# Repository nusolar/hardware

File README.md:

# hardware
schematics, board files, BOMs

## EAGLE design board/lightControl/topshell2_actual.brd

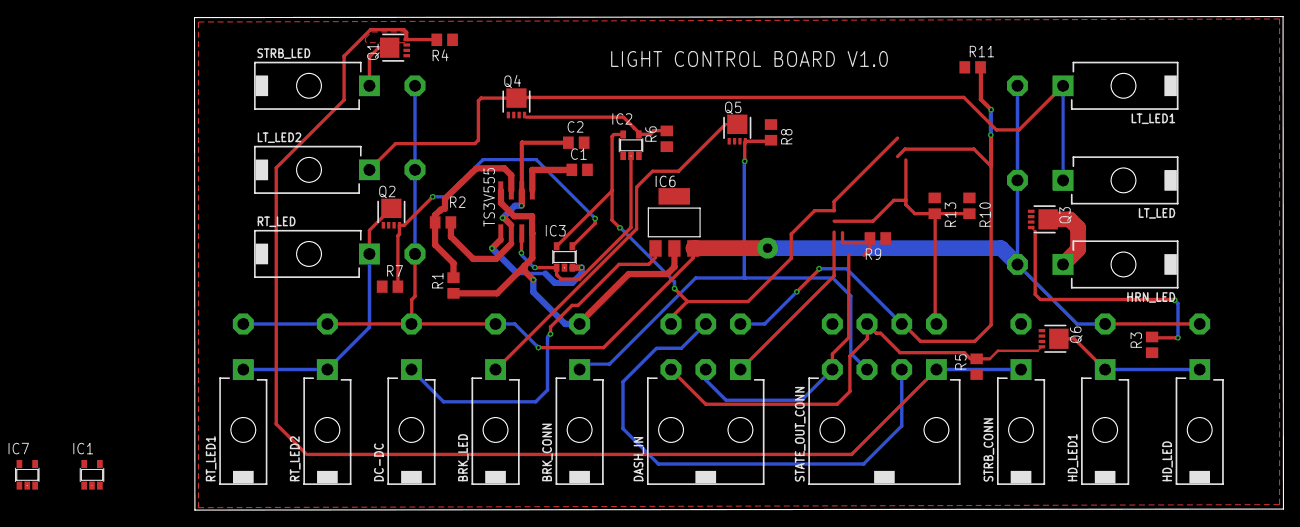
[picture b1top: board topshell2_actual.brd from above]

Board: 2 copper layers, 131.6 x 59.6 mm, 42 parts (0 on the bottom side), 26 nets.

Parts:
BRK_CONN: 39-30-02?; 39-30-?02?
BRK_LED: 39-30-02?; 39-30-?02?
C1: 10nF; C0805
C2: 2.2uF; C0805
DASH_IN: 39-30-06?; 39-30-?06?
DC-DC: 39-30-02?; 39-30-?02?
HD_LED, HD_LED1: 39-30-02?; 39-30-?02?
HRN_LED: 39-30-02?; 39-30-?02?
IC1, IC7: 74AHC1G32DBV; SOT23-5
IC2, IC3: 74AHC1G08DBV; SOT23-5
IC6: REG1117; SOT223
LT_LED, LT_LED1, LT_LED2: 39-30-02?; 39-30-?02?
Q1, Q2, Q3, Q4, Q5, Q6: PSMN013-30MLC; LFPAK33
R1: 100K; R0805
R2: 220K; R0805
R3, R4, R5, R6, R7, R8, R9, R10, R11, R13: 1K; R0805
RT_LED, RT_LED1, RT_LED2: 39-30-02?; 39-30-?02?
STATE_OUT_CONN: 39-30-08?; 39-30-?08?
STRB_CONN: 39-30-02?; 39-30-?02?
STRB_LED: 39-30-02?; 39-30-?02?
TS3V555: LM555D; SO08

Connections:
GND: C1.2, C2.2, IC1.3, IC2.3, IC3.3, IC7.3, Q1.1, Q1.2, Q1.3, Q2.1, Q2.2, Q2.3, Q3.1, Q3.2, Q3.3, Q4.1, Q4.2, Q4.3, Q5.1, Q5.2, Q5.3, Q6.1, Q6.2, Q6.3, R3.1, R4.1, R5.1, R6.1, R7.1, R8.1, R9.1, R10.1, R11.1, R13.1, STATE_OUT_CONN.8, STRB_CONN.2, TS3V555.1
unnamed: R1.2, R2.1, TS3V555.7
unnamed: Q1.MB, STRB_LED.1
unnamed: C2.1, R2.2, TS3V555.2, TS3V555.6
unnamed: IC2.2, IC3.1, TS3V555.3
unnamed: HRN_LED.1, Q3.MB
unnamed: Q1.4, R4.2, STATE_OUT_CONN.1, STRB_CONN.1
unnamed: DASH_IN.2, IC1.2, R9.2, STATE_OUT_CONN.4
unnamed: DASH_IN.1, IC1.1, IC7.2, R10.2, R13.2, STATE_OUT_CONN.5
unnamed: IC1.4, IC2.1
unnamed: IC3.2, IC7.4
unnamed: DASH_IN.4, IC7.1, R11.2, STATE_OUT_CONN.6
unnamed: IC2.4, Q4.4, R6.2
unnamed: IC3.4, Q2.4, R7.2
unnamed: LT_LED.1, LT_LED1.1, LT_LED2.1, Q4.MB
unnamed: Q2.MB, RT_LED.1, RT_LED1.1, RT_LED2.1
unnamed: BRK_LED.1, Q5.MB
unnamed: HD_LED.1, HD_LED1.1, Q6.MB
unnamed: DC-DC.1, IC6.1
unnamed: DASH_IN.3, Q6.4, R5.2, STATE_OUT_CONN.7
unnamed: Q3.4, R3.2
unnamed: DASH_IN.5, STATE_OUT_CONN.2
unnamed: BRK_CONN.1, Q5.4, R8.2, STATE_OUT_CONN.3
unnamed: BRK_LED.2, DC-DC.2, HD_LED.2, HD_LED1.2, HRN_LED.2, IC6.3, LT_LED.2, LT_LED1.2, LT_LED2.2, RT_LED.2, RT_LED1.2, RT_LED2.2, STRB_LED.2
TS3V555: C1.1, TS3V555.5
VDD: BRK_CONN.2, DASH_IN.6, IC1.5, IC2.5, IC3.5, IC6.2, IC7.5, R1.1, TS3V555.4, TS3V555.8

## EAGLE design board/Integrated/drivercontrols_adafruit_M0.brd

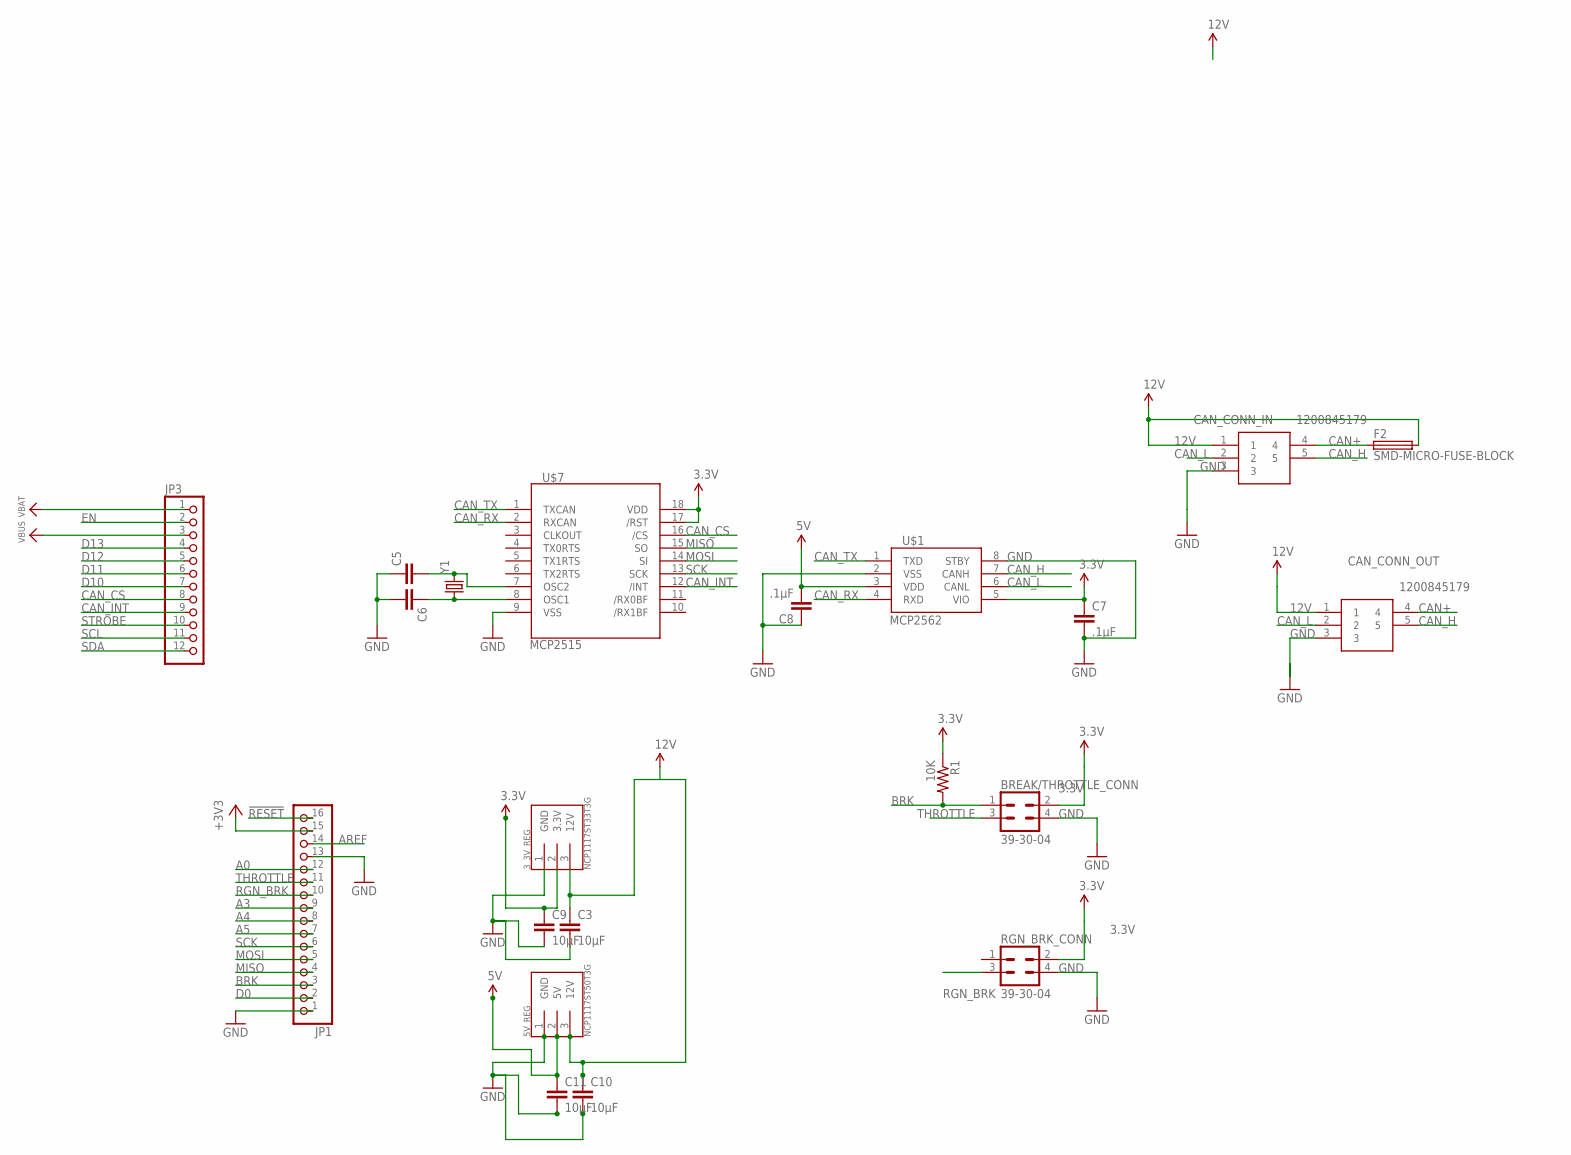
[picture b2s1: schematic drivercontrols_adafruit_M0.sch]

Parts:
3_3V_REG: NCP1117ST33T3G; SOT223
5V_REG: NCP1117ST50T3G; SOT223
BREAK/THROTTLE_CONN: 39-30-04; 39-30-?04?
C3, C9, C10, C11: 10µF; 0805
C5, C6: CAP0805; 0805
C7, C8: .1µF; 0805
CAN_CONN_IN: 1200845179
CAN_CONN_OUT: 1200845179
F2: SMD-MICRO-FUSE-BLOCK; OMNIBLOK
JP1: HEADER-1X16ROUND; 1X16_ROUND
JP3: HEADER-1X12; 1X12_ROUND
R1: 10K; M0805
RGN_BRK_CONN: 39-30-04; 39-30-?04?
U$1: MCP2562; SOIC8
U$7: MCP2515; SO-18W
Y1: CRYSTALHC49US; HC49US

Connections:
3.3V: 3_3V_REG.2 (3.3V), BREAK/THROTTLE_CONN.2, C7.1, C9.1, R1.1, RGN_BRK_CONN.2, U$1.5 (VIO), U$7.17 (/RST), U$7.18 (VDD)
5V: 5V_REG.2 (5V), C8.2, C11.1, U$1.3 (VDD)
12V: 3_3V_REG.3 (12V), 5V_REG.3 (12V), C3.1, C10.1, CAN_CONN_IN.1, CAN_CONN_OUT.1, F2.P$2 (2)
!RESET: JP1.16
+3V3: JP1.15
A0: JP1.12
A3: JP1.9
A4: JP1.8
A5: JP1.7
AREF: JP1.14
BRK: BREAK/THROTTLE_CONN.1, JP1.3, R1.2
CAN+: CAN_CONN_IN.4, CAN_CONN_OUT.4, F2.P$1 (1)
CAN_CS: JP3.8, U$7.16 (/CS)
CAN_H: CAN_CONN_IN.5, CAN_CONN_OUT.5, U$1.7 (CANH)
CAN_INT: JP3.9, U$7.12 (/INT)
CAN_L: CAN_CONN_IN.2, CAN_CONN_OUT.2, U$1.6 (CANL)
CAN_RX: U$1.4 (RXD), U$7.2 (RXCAN)
CAN_TX: U$1.1 (TXD), U$7.1 (TXCAN)
D0: JP1.2
D10: JP3.7
D11: JP3.6
D12: JP3.5
D13: JP3.4
EN: JP3.2
GND: 3_3V_REG.1 (GND), 5V_REG.1 (GND), BREAK/THROTTLE_CONN.4, C3.2, C5.1, C6.2, C7.2, C8.1, C9.2, C10.2, C11.2, CAN_CONN_IN.3, CAN_CONN_OUT.3, JP1.1, JP1.13, RGN_BRK_CONN.4, U$1.2 (VSS), U$1.8 (STBY), U$7.9 (VSS)
MISO: JP1.4, U$7.15 (SO)
MOSI: JP1.5, U$7.14 (SI)
unnamed: C5.2, U$7.7 (OSC2), Y1.2
unnamed: C6.1, U$7.8 (OSC1), Y1.1
RGN_BRK: JP1.10, RGN_BRK_CONN.3
SCK: JP1.6, U$7.13 (SCK)
SCL: JP3.11
SDA: JP3.12
STROBE: JP3.10
THROTTLE: BREAK/THROTTLE_CONN.3, JP1.11
VBAT: JP3.1
VBUS: JP3.3

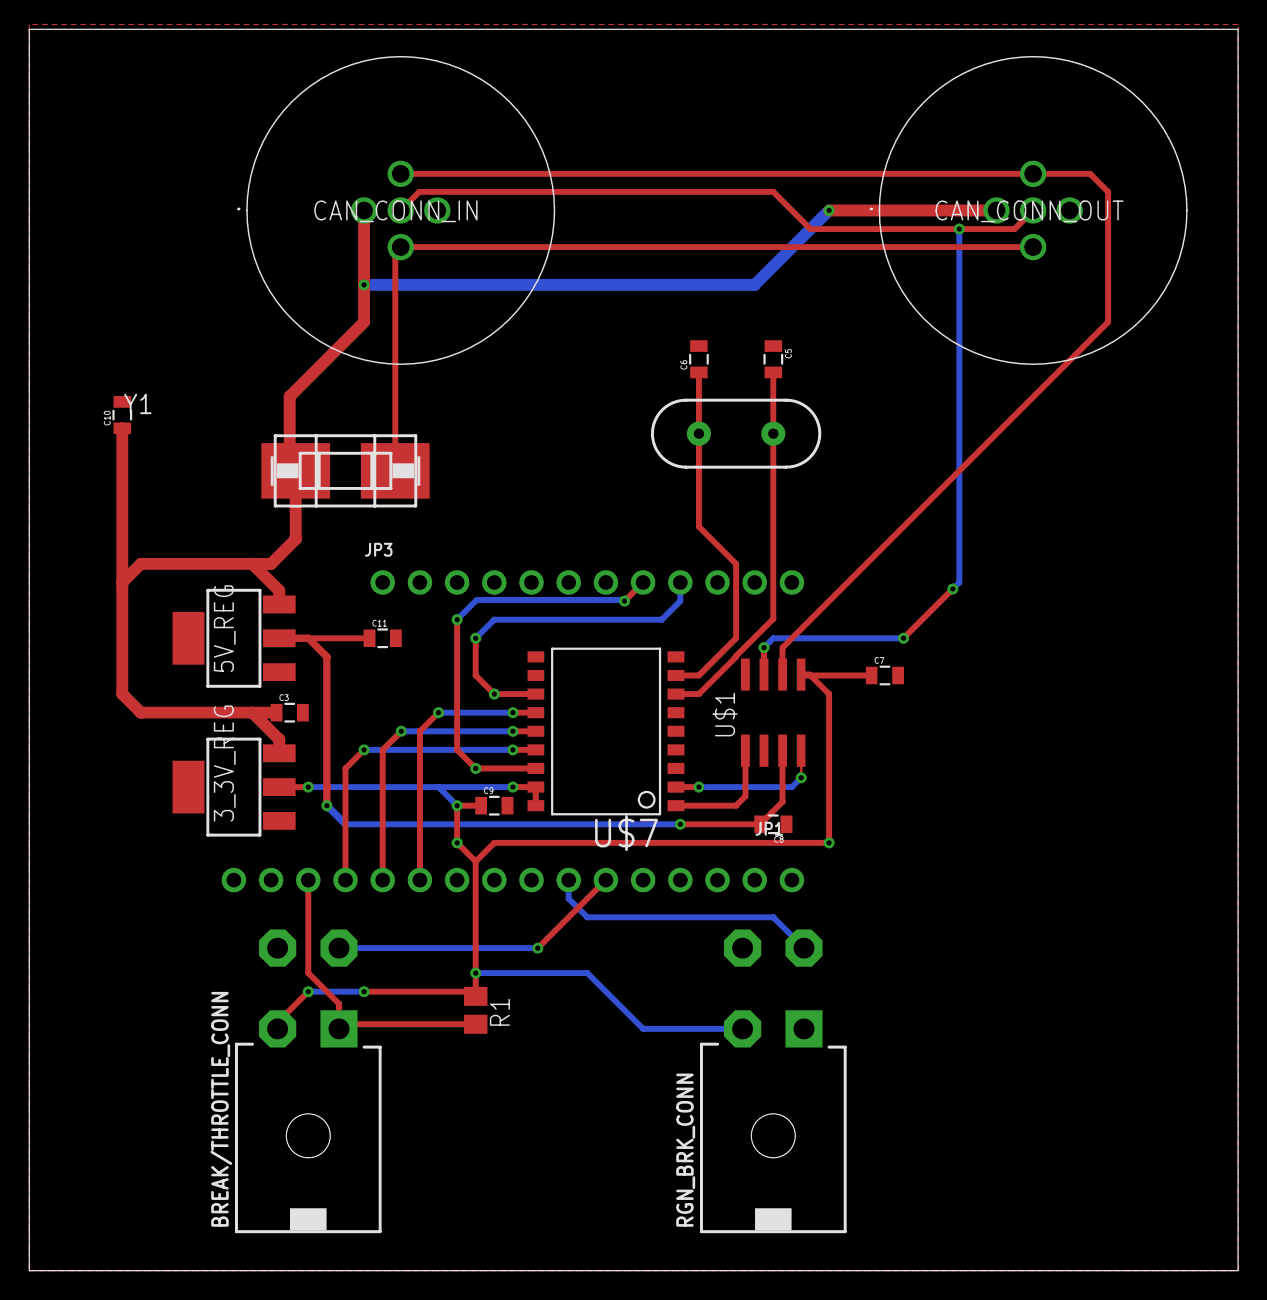
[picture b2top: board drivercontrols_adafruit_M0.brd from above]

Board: 2 copper layers, 82.5 x 84.8 mm, 21 parts (0 on the bottom side), 19 nets.

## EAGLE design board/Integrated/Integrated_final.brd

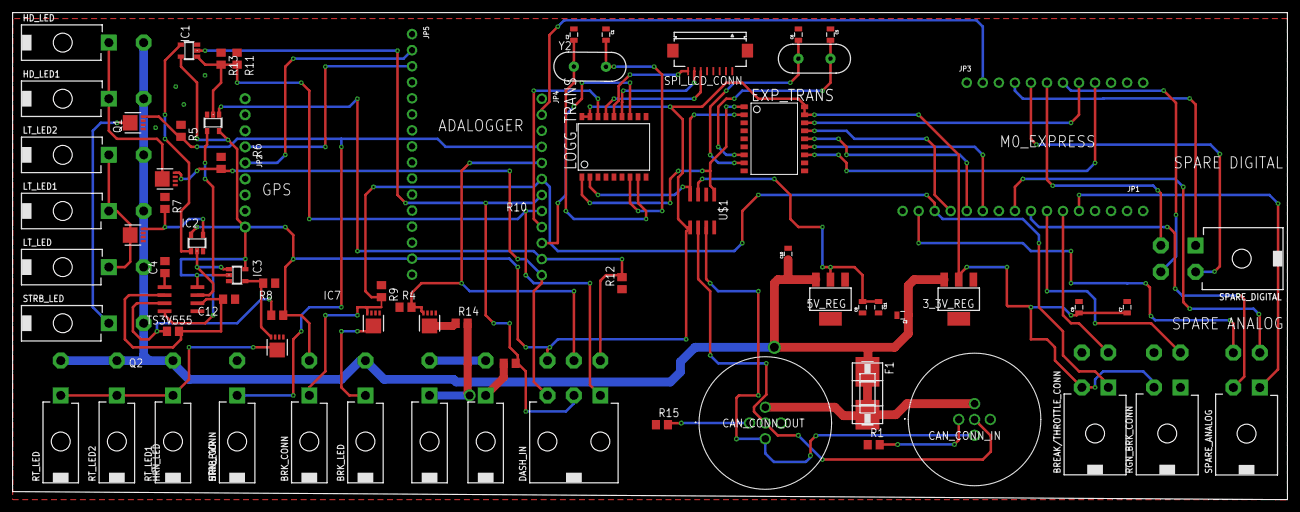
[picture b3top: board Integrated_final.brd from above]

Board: 2 copper layers, 201.9 x 77.1 mm, 73 parts (0 on the bottom side), 60 nets.

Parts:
3_3V_REG: NCP1117ST33T3G; SOT223
5V_REG: NCP1117ST50T3G; SOT223
BREAK/THROTTLE_CONN: 39-30-04?; 39-30-?04?
BRK_CONN: 39-30-02?; 39-30-?02?
BRK_LED: 39-30-02?; 39-30-?02?
C1, C2, C5, C6: 18 pF; 0805
C3, C9, C10, C11: 10µF; 0805
C4: 10nF; C0805
C7, C8: .1µF; 0805
C12: 2.2uF; C0805
CAN_CONN_IN: 1200845179
CAN_CONN_OUT: 1200845179
DASH_IN: 39-30-06?; 39-30-?06?
EXP_TRANS: MCP2515; SO-18W
F1: SMD-MICRO-FUSE-BLOCK; OMNIBLOK
HD_LED, HD_LED1: 39-30-02?; 39-30-?02?
HRN_LED: 39-30-02?; 39-30-?02?
HRN_PWR: 39-30-02?; 39-30-?02?
IC1, IC7: 74AHC1G32DBV; SOT23-5
IC2, IC3: 74AHC1G08DBV; SOT23-5
JP1, JP5: 1X16_ROUND
JP2: 1X09_ROUND_70
JP3, JP4: 1X12_ROUND
LOGG_TRANS: MCP2515; SO-18W
LT_LED, LT_LED1, LT_LED2: 39-30-02?; 39-30-?02?
Q1, Q2, Q3, Q4, Q5, Q6: PSMN013-30MLC; LFPAK33
R1, R15: 0; R0805
R2: 220K; R0805
R3: 100K; R0805
R4, R5, R6, R7, R8, R9, R10, R11, R12, R13, R14: 1K; R0805
RGN_BRK_CONN: 39-30-04?; 39-30-?04?
RT_LED, RT_LED1, RT_LED2: 39-30-02?; 39-30-?02?
SPARE_ANALOG: 39-30-04?; 39-30-?04?
SPARE_DIGITAL: 39-30-04?; 39-30-?04?
SPI_LCD_CONN: FH12-08S-1SH
STRB_CONN: 39-30-02?; 39-30-?02?
STRB_LED: 39-30-02?; 39-30-?02?
TS3V555: LM555D; SO08
U$1: MCP2562; SOIC8
Y1, Y2: HC49US

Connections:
3.3V: 3_3V_REG.2, BREAK/THROTTLE_CONN.2, BRK_CONN.2, C7.1, C9.1, DASH_IN.6, EXP_TRANS.17, EXP_TRANS.18, IC1.5, IC2.5, IC3.5, IC7.5, JP2.9, JP5.15, LOGG_TRANS.17, LOGG_TRANS.18, R3.1, RGN_BRK_CONN.2, TS3V555.4, TS3V555.8, U$1.5
5V: 5V_REG.2, C8.2, C11.1, U$1.3
12V: 3_3V_REG.3, 5V_REG.3, BRK_LED.2, C3.1, C10.1, CAN_CONN_IN.2, CAN_CONN_OUT.2, F1.P$1, F1.P$2, HD_LED.2, HD_LED1.2, LT_LED.2, LT_LED1.2, LT_LED2.2, RT_LED.2, RT_LED1.2, RT_LED2.2, STRB_LED.2
A0: JP1.12, SPARE_ANALOG.1
A3: JP1.9, SPARE_ANALOG.2
A4: JP1.8, SPARE_ANALOG.3
BRK: BREAK/THROTTLE_CONN.1, BRK_CONN.1, JP1.3, JP4.6, Q5.4, R9.2
CAN_CS: EXP_TRANS.16, JP3.8
CAN_CS_LOG: JP4.9, LOGG_TRANS.16
CAN_H: CAN_CONN_IN.4, CAN_CONN_OUT.4, U$1.7
CAN_INT: EXP_TRANS.12, JP3.9
CAN_INT_LOG: JP4.10, LOGG_TRANS.12
CAN_L: CAN_CONN_IN.5, CAN_CONN_OUT.5, U$1.6
CAN_RX: EXP_TRANS.2, LOGG_TRANS.2, U$1.4
CAN_SHIELD: CAN_CONN_OUT.1, R15.2
CAN_SHIELD_2: CAN_CONN_IN.1, R1.2
CAN_TX: EXP_TRANS.1, LOGG_TRANS.1, U$1.1
D0: JP1.2, SPARE_ANALOG.4
D9(LOG): DASH_IN.1, IC1.1, IC7.2, JP4.8, R11.2, R13.2
D10: JP3.7, SPARE_DIGITAL.4
D10(LOG): DASH_IN.2, IC1.2, JP4.7, R10.2
D11: JP3.6, SPARE_DIGITAL.3
D12: JP3.5, SPARE_DIGITAL.2
D12(LOG): DASH_IN.5, JP4.5, Q3.4, R4.2
D13: JP3.4, SPARE_DIGITAL.1
D13(LOG): JP4.4, Q1.4, R5.2, STRB_CONN.1
EN: JP3.2, JP4.2
GND: 3_3V_REG.1, 5V_REG.1, BREAK/THROTTLE_CONN.4, C1.1, C2.2, C3.2, C4.2, C5.1, C6.2, C7.2, C8.1, C9.2, C10.2, C11.2, C12.2, CAN_CONN_IN.3, CAN_CONN_OUT.3, EXP_TRANS.9, HRN_PWR.1, IC1.3, IC2.3, IC3.3, IC7.3, JP1.1, JP1.13, JP2.3, JP5.1, JP5.13, LOGG_TRANS.9, Q1.1, Q1.2, Q1.3, Q2.1, Q2.2, Q2.3, Q3.1, Q3.2, Q3.3, Q4.1, Q4.2, Q4.3, Q5.1, Q5.2, Q5.3, Q6.1, Q6.2, Q6.3, R1.1, R4.1, R5.1, R6.1, R7.1, R8.1, R9.1, R10.1, R11.1, R12.1, R13.1, R15.1, RGN_BRK_CONN.4, SPI_LCD_CONN.1, STRB_CONN.2, TS3V555.1, U$1.2, U$1.8
MISO: EXP_TRANS.15, JP1.4
MISO_LOG: LOGG_TRANS.15, SPI_LCD_CONN.6
MOSI: EXP_TRANS.14, JP1.5
MOSI_LOG: LOGG_TRANS.14, SPI_LCD_CONN.8
unnamed: C5.2, EXP_TRANS.7, Y1.2
unnamed: C2.1, LOGG_TRANS.8, Y2.1
unnamed: C1.2, LOGG_TRANS.7, Y2.2
unnamed: R2.1, R3.2, TS3V555.7
unnamed: C12.1, R2.2, TS3V555.2, TS3V555.6
unnamed: IC2.2, IC3.1, TS3V555.3
unnamed: C6.1, EXP_TRANS.8, Y1.1
unnamed: IC2.4, Q4.4, R7.2
unnamed: IC3.4, Q2.4, R8.2
unnamed: LT_LED.1, LT_LED1.1, LT_LED2.1, Q4.MB
unnamed: Q2.MB, RT_LED.1, RT_LED1.1, RT_LED2.1
unnamed: HD_LED.1, HD_LED1.1, Q6.MB
unnamed: Q1.MB, STRB_LED.1
unnamed: BRK_LED.1, Q5.MB
unnamed: IC1.4, IC2.1
unnamed: IC3.2, IC7.4
unnamed: HRN_LED.2, HRN_PWR.2
unnamed: HRN_LED.1, R14.2
unnamed: Q3.MB, R14.1
RGN_BRK: JP1.10, RGN_BRK_CONN.3
RX: JP2.4, JP5.3
SCK: EXP_TRANS.13, JP1.6
SCK_LOG: LOGG_TRANS.13, SPI_LCD_CONN.7
SCL_LOG: DASH_IN.4, IC7.1, JP4.11, R12.2
SDA_LOG: DASH_IN.3, JP4.12, Q6.4, R6.2
THROTTLE: BREAK/THROTTLE_CONN.3, JP1.11
TS3V555: C4.1, TS3V555.5
TX: JP2.5, JP5.2

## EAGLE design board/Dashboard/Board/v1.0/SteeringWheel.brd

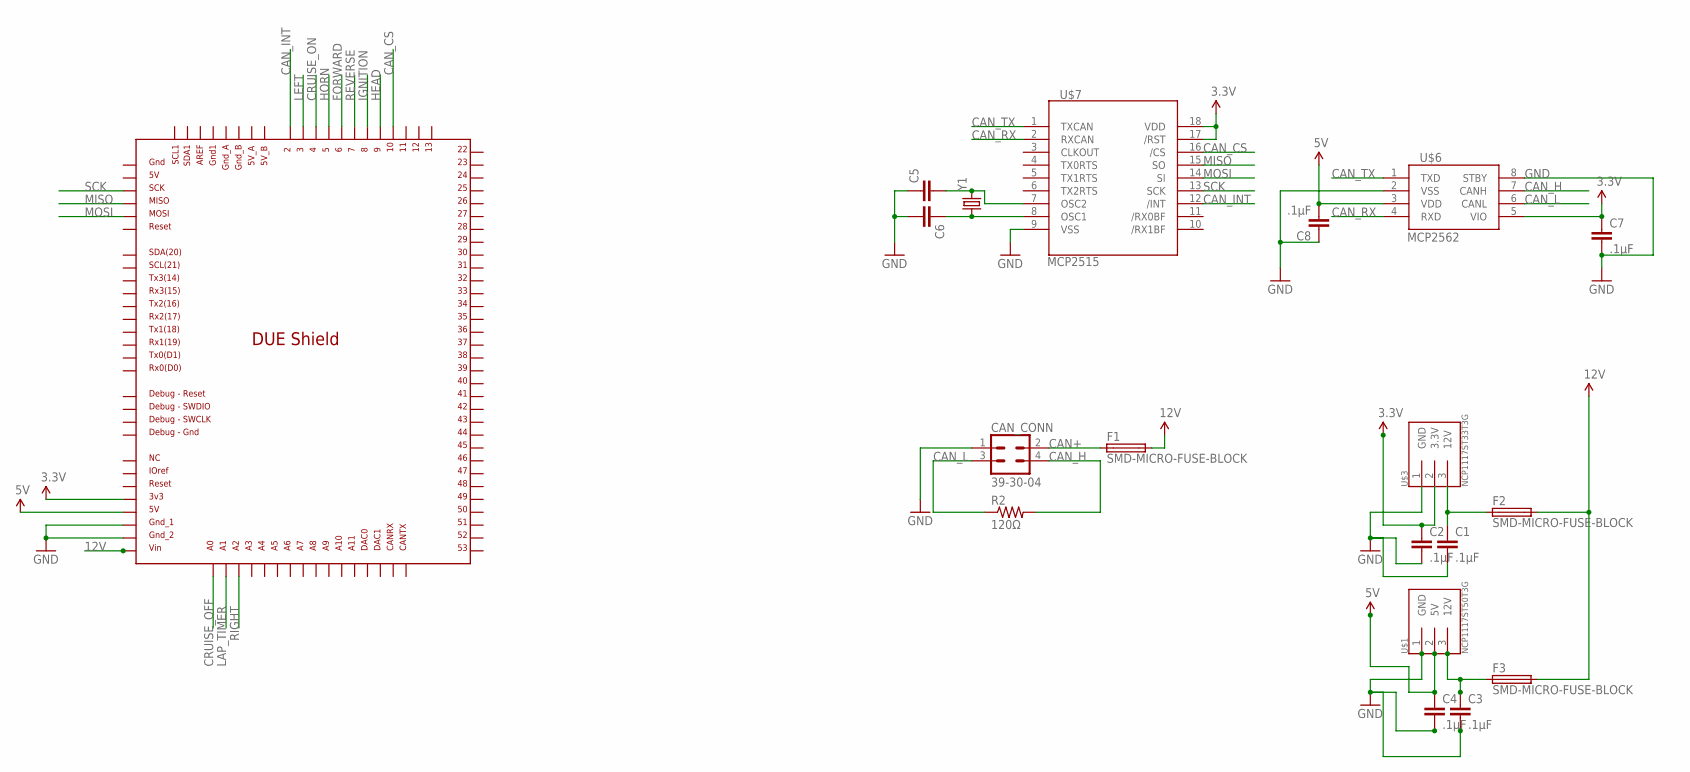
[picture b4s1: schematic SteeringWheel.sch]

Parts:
C1, C2, C3, C4, C7, C8: .1µF; 0805
C5, C6: CAP0805; 0805
CAN_CONN: 39-30-04; 39-30-?04?
F1, F2, F3: SMD-MICRO-FUSE-BLOCK; OMNIBLOK
R2: 120Ω; 0805
U$1: NCP1117ST50T3G; SOT223
U$2: DUE(NORMAL)
U$3: NCP1117ST33T3G; SOT223
U$6: MCP2562; SOIC8
U$7: MCP2515; SO-18W
Y1: CRYSTALHC49US; HC49US

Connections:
3.3V: C2.1, C7.1, U$2.3V3, U$3.2 (3.3V), U$6.5 (VIO), U$7.17 (/RST), U$7.18 (VDD)
5V: C4.1, C8.2, U$1.2 (5V), U$2.5V, U$6.3 (VDD)
12V: F1.P$2 (2), F2.P$2 (2), F3.P$2 (2), U$2.VIN
CAN+: CAN_CONN.2, F1.P$1 (1)
CAN_CS: U$2.10, U$7.16 (/CS)
CAN_H: CAN_CONN.4, R2.2, U$6.7 (CANH)
CAN_INT: U$2.2, U$7.12 (/INT)
CAN_L: CAN_CONN.3, R2.1, U$6.6 (CANL)
CAN_RX: U$6.4 (RXD), U$7.2 (RXCAN)
CAN_TX: U$6.1 (TXD), U$7.1 (TXCAN)
CRUISE_OFF: U$2.A0
CRUISE_ON: U$2.4
FORWARD: U$2.6
GND: C1.2, C2.2, C3.2, C4.2, C5.1, C6.2, C7.2, C8.1, CAN_CONN.1, U$1.1 (GND), U$2.GND_1, U$2.GND_2, U$3.1 (GND), U$6.2 (VSS), U$6.8 (STBY), U$7.9 (VSS)
HEAD: U$2.9
HORN: U$2.5
IGNITION: U$2.8
LAP_TIMER: U$2.A1
LEFT: U$2.3
MISO: U$2.MISO_ICSP, U$7.15 (SO)
MOSI: U$2.MOSI_ICSP, U$7.14 (SI)
unnamed: C3.1, F3.P$1 (1), U$1.3 (12V)
unnamed: C1.1, F2.P$1 (1), U$3.3 (12V)
unnamed: C5.2, U$7.7 (OSC2), Y1.2
unnamed: C6.1, U$7.8 (OSC1), Y1.1
REVERSE: U$2.7
RIGHT: U$2.A2
SCK: U$2.SCK_ICSP, U$7.13 (SCK)

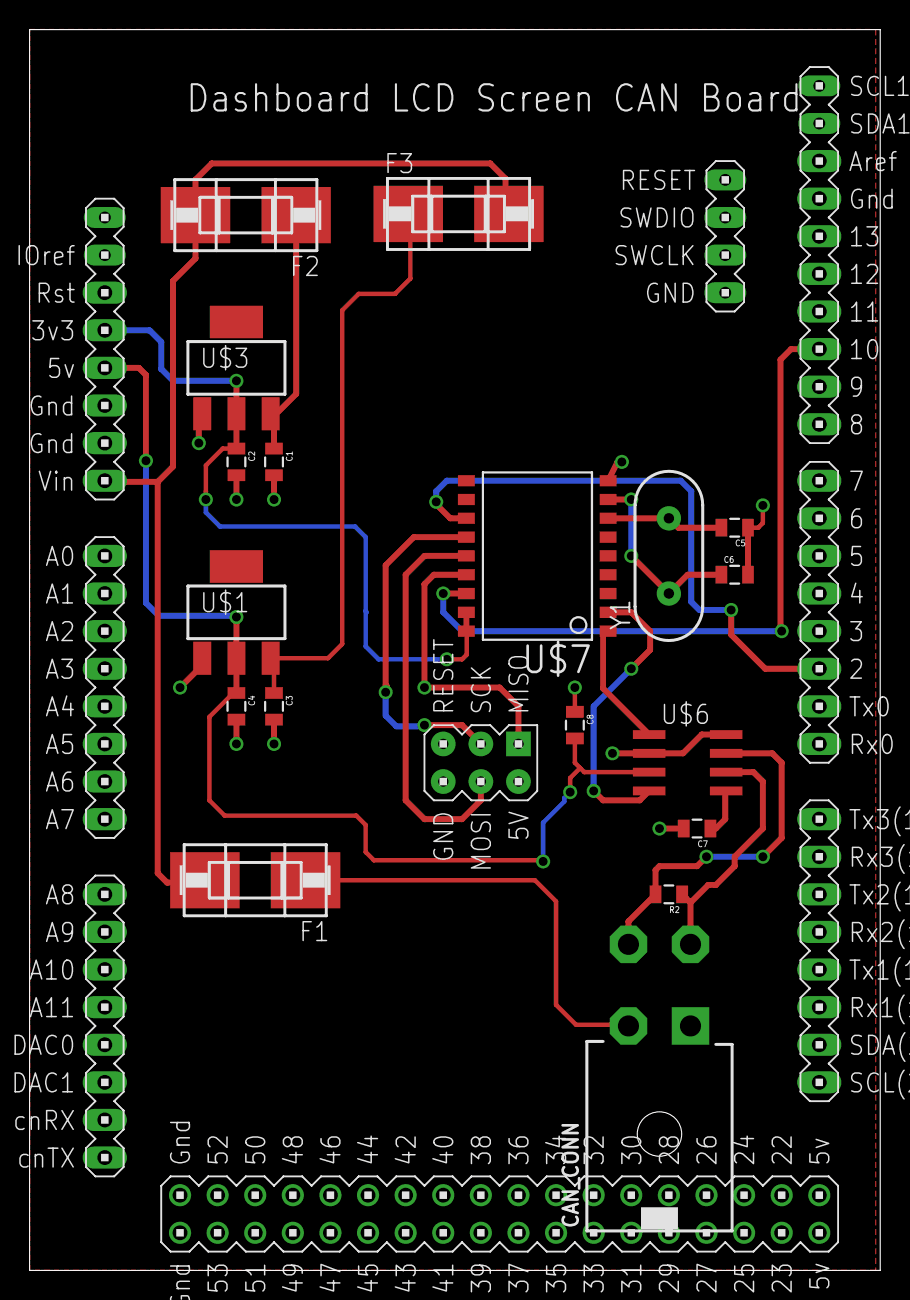
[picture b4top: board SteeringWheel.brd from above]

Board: 2 copper layers, 57.5 x 83.8 mm, 19 parts (0 on the bottom side), 18 nets.

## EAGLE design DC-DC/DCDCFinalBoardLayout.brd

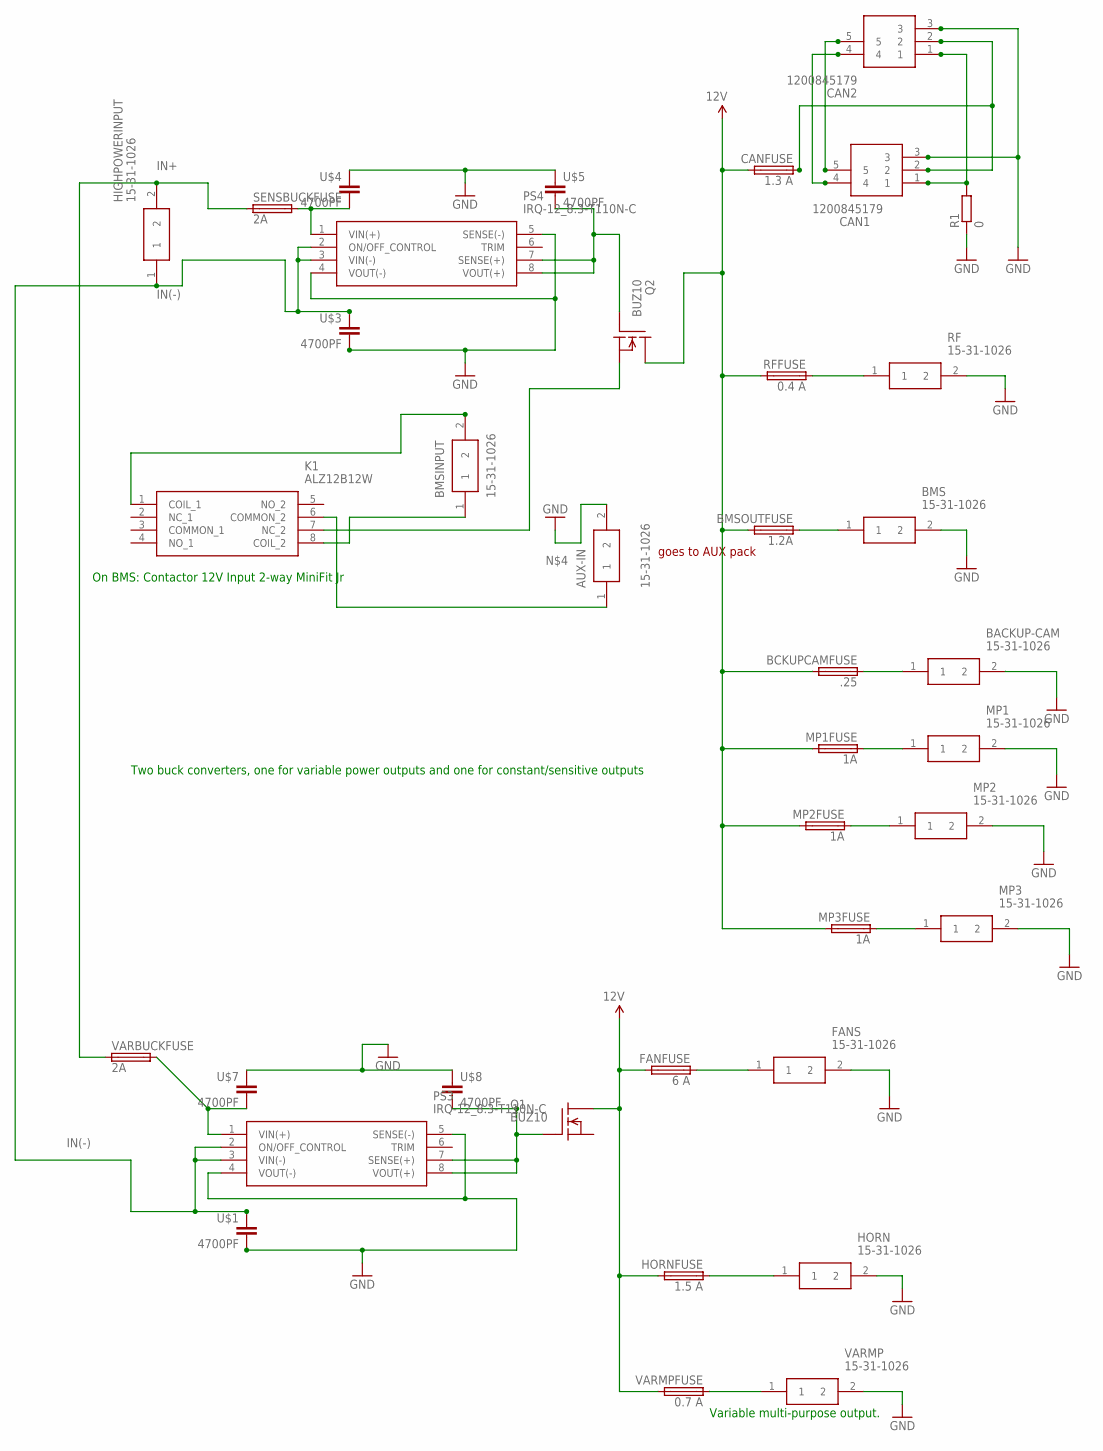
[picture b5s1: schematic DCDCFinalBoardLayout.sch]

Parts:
AUX-IN: 15-31-1026; 15311026
BACKUP-CAM: 15-31-1026; 15311026
BCKUPCAMFUSE: .25; OMNIBLOK
BMS: 15-31-1026; 15311026
BMSINPUT: 15-31-1026; 15311026
BMSOUTFUSE: 1.2A; OMNIBLOK
CAN1, CAN2: 1200845179
CANFUSE: 1.3 A; OMNIBLOK
FANFUSE: 6 A; OMNIBLOK
FANS: 15-31-1026; 15311026
HIGHPOWERINPUT: 15-31-1026; 15311026
HORN: 15-31-1026; 15311026
HORNFUSE: 1.5 A; OMNIBLOK
K1: ALZ12B12W
MP1, MP2, MP3: 15-31-1026; 15311026
MP1FUSE, MP2FUSE, MP3FUSE: 1A; OMNIBLOK
PS3, PS4: IRQ-12_8.3-T110N-C; IRQ1283T110NC
Q1, Q2: BUZ10; TO220
R1: 0; R0805
RF: 15-31-1026; 15311026
RFFUSE: 0.4 A; OMNIBLOK
SENSBUCKFUSE: 2A; OMNIBLOK
U$1, U$3, U$4, U$5, U$7, U$8: 4700PF; Y2_CAP
VARBUCKFUSE: 2A; OMNIBLOK
VARMP: 15-31-1026; 15311026
VARMPFUSE: 0.7 A; OMNIBLOK

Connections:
12V: BCKUPCAMFUSE.P$2 (2), BMSOUTFUSE.P$2 (2), CANFUSE.P$2 (2), FANFUSE.P$2 (2), HORNFUSE.P$2 (2), MP1FUSE.P$2 (2), MP2FUSE.P$2 (2), MP3FUSE.P$2 (2), Q1.2 (D), Q2.2 (D), RFFUSE.P$2 (2), VARMPFUSE.P$2 (2)
CAN+: BACKUP-CAM.1, BCKUPCAMFUSE.P$1 (1)
GND: AUX-IN.2, BACKUP-CAM.2, BMS.2, CAN1.3, CAN2.3, FANS.2, HORN.2, MP1.2, MP2.2, MP3.2, PS3.4 (VOUT(-)), PS3.5 (SENSE(-)), PS4.4 (VOUT(-)), PS4.5 (SENSE(-)), R1.1, RF.2, U$1.P$2 (2), U$3.P$2 (2), U$4.P$1 (1), U$5.P$1 (1), U$7.P$1 (1), U$8.P$1 (1), VARMP.2
IN(-): HIGHPOWERINPUT.1, PS3.2 (ON/OFF_CONTROL), PS3.3 (VIN(-)), PS4.2 (ON/OFF_CONTROL), PS4.3 (VIN(-)), U$1.P$1 (1), U$3.P$1 (1)
IN+: HIGHPOWERINPUT.2, SENSBUCKFUSE.P$1 (1), VARBUCKFUSE.P$1 (1)
unnamed: HORN.1, HORNFUSE.P$1 (1)
unnamed: AUX-IN.1, K1.6 (COMMON_2)
unnamed: BMSINPUT.1, K1.8 (COIL_2)
unnamed: BMSINPUT.2, K1.1 (COIL_1), K1.7 (NC_2), Q2.3 (S)
unnamed: PS3.1 (VIN(+)), U$7.P$2 (2), VARBUCKFUSE.P$2 (2)
unnamed: VARMP.1, VARMPFUSE.P$1 (1)
unnamed: RF.1, RFFUSE.P$1 (1)
unnamed: FANFUSE.P$1 (1), FANS.1
unnamed: PS4.1 (VIN(+)), SENSBUCKFUSE.P$2 (2), U$4.P$2 (2)
unnamed: BMS.1, BMSOUTFUSE.P$1 (1)
unnamed: MP2.1, MP2FUSE.P$1 (1)
unnamed: MP3.1, MP3FUSE.P$1 (1)
unnamed: PS3.7 (SENSE(+)), PS3.8 (VOUT(+)), Q1.1 (G), U$8.P$2 (2)
unnamed: MP1.1, MP1FUSE.P$1 (1)
unnamed: PS4.7 (SENSE(+)), PS4.8 (VOUT(+)), Q2.1 (G), U$5.P$2 (2)
unnamed: CAN1.1, CAN2.1, R1.2
unnamed: CAN1.4, CAN2.4
unnamed: CAN1.5, CAN2.5
unnamed: CAN1.2, CAN2.2, CANFUSE.P$1 (1)

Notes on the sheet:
On BMS: Contactor 12V Input 2-way MiniFit Jr
goes to AUX pack
Variable multi-purpose output.
Two buck converters, one for variable power outputs and one for constant/sensitive outputs

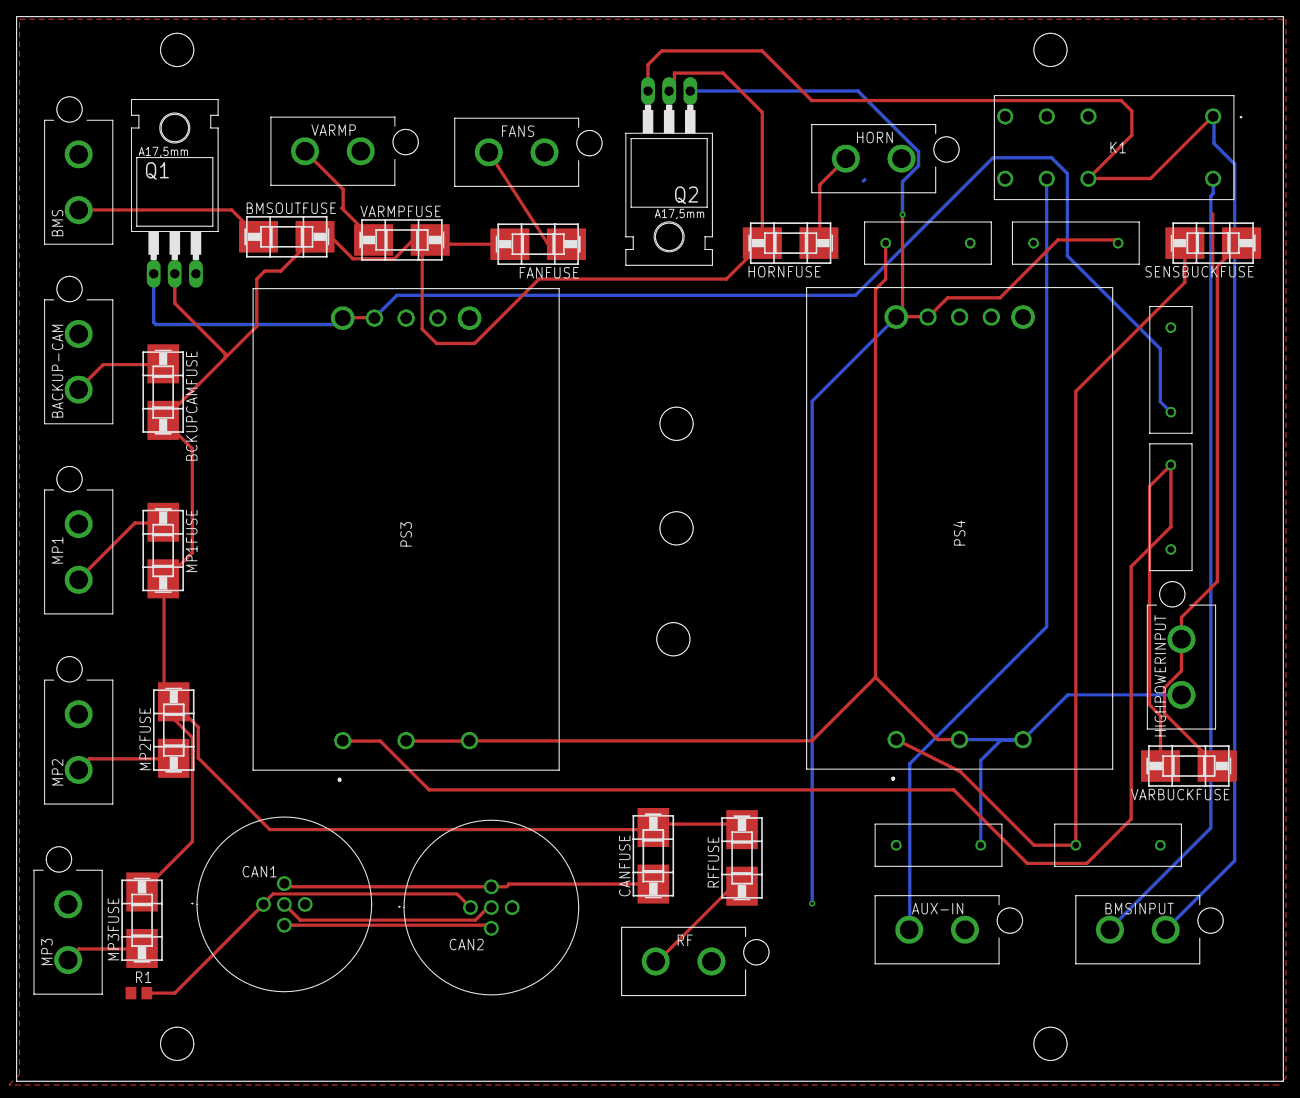
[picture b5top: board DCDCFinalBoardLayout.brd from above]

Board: 2 copper layers, 152.3 x 128.0 mm, 38 parts (0 on the bottom side), 24 nets.

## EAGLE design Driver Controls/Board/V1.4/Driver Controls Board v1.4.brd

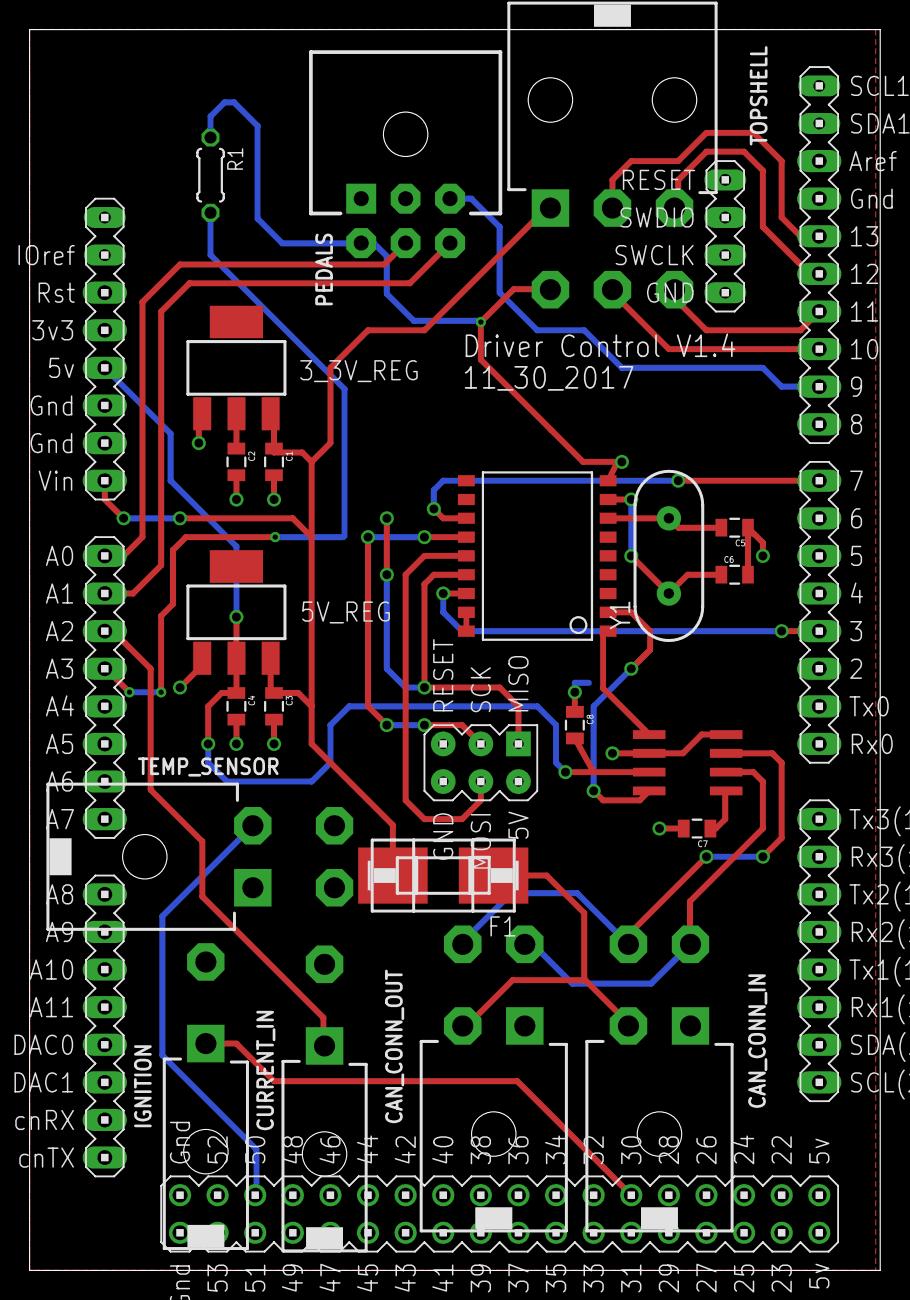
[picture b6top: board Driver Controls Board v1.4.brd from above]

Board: 2 copper layers, 57.5 x 83.8 mm, 23 parts (0 on the bottom side), 27 nets.

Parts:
3_3V_REG: NCP1117ST33T3G; SOT223
5V_REG: NCP1117ST50T3G; SOT223
C1, C2, C3, C4: 10µF; 0805
C5, C6: 0805
C7, C8: .1µF; 0805
CAN_CONN_IN: 39-30-04?; 39-30-?04?
CAN_CONN_OUT: 39-30-04?; 39-30-?04?
CURRENT_IN: 39-30-02?_S; 39-30-?02?
F1: SMD-MICRO-FUSE-BLOCK; OMNIBLOK
IGNITION: 39-30-02?_S; 39-30-?02?
PEDALS: 43045-06_S; 43045-06
R1: 0204/5
TEMP_SENSOR: 39-30-04?; 39-30-?04?
TOPSHELL: 39-30-06?_S; 39-30-?06?
U$2: DUE(NORMAL)
U$6: MCP2562; SOIC8
U$7: MCP2515; SO-18W
Y1: HC49US

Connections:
3.3V: 3_3V_REG.2, C2.1, C7.1, PEDALS.1, TEMP_SENSOR.1, U$2.3V3, U$6.5, U$7.17, U$7.18
5V: 5V_REG.2, C4.1, C8.2, U$2.5V, U$6.3
12V: 3_3V_REG.3, 5V_REG.3, C1.1, C3.1, F1.P$2, TOPSHELL.1, U$2.VIN
ACCEL: PEDALS.5, U$2.A0
BRAKE: TOPSHELL.2, U$2.13
BRAKE_PED: PEDALS.3, U$2.9
CAN+: CAN_CONN_IN.2, CAN_CONN_OUT.2, F1.P$1
CAN_CS: U$2.3, U$7.16
CAN_H: CAN_CONN_IN.4, CAN_CONN_OUT.4, U$6.7
CAN_INT: U$2.7, U$7.12
CAN_L: CAN_CONN_IN.3, CAN_CONN_OUT.3, U$6.6
CAN_RX: U$6.4, U$7.2
CAN_TX: U$6.1, U$7.1
CUR_IN: CURRENT_IN.1, U$2.A2
GND: 3_3V_REG.1, 5V_REG.1, C1.2, C2.2, C3.2, C4.2, C5.1, C6.2, C7.2, C8.1, CAN_CONN_IN.1, CAN_CONN_OUT.1, CURRENT_IN.2, IGNITION.2, PEDALS.4, R1.1, TEMP_SENSOR.3, TOPSHELL.4, U$2.GND_1, U$2.GND_2, U$6.2, U$6.8, U$7.9
HEADLIGHTS: TOPSHELL.5, U$2.10
IGNITION: IGNITION.1, U$2.30
L_TURN: TOPSHELL.3, U$2.12
MISO: U$2.MISO_ICSP, U$7.15
MOSI: U$2.MOSI_ICSP, U$7.14
unnamed: R1.2, U$2.A3
unnamed: C5.2, U$7.7, Y1.2
unnamed: C6.1, U$7.8, Y1.1
REGEN: PEDALS.6, U$2.A1
R_TURN: TOPSHELL.6, U$2.11
SCK: U$2.SCK_ICSP, U$7.13
SENSOR_IN: TEMP_SENSOR.2, U$2.50

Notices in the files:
parts and their libraries:
SparkFun-Aesthetics: Licensing: Creative Commons ShareAlike 4.0 International - https://creativecommons.org/licenses/by-sa/4.0
con-molex-mini-fit: Copyright (C) 2011, Bob Starr
transistor-power: PSMN013-30MLC © NXP B.V. 2012. All rights reserved.
